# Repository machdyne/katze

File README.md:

# Katze Ethernet Pmod&trade; compatible module

Katze is a 10/100 Ethernet PHY PMOD designed to be compatible with LiteX.

This repo contains schematics, pinouts and usage examples.

Find more information on the [Katze product page](https://machdyne.com/product/katze-ethernet-pmod/).

## Usage

### Example Litex Platform Configuration

```
	("eth_clocks", 0,
		Subsignal("ref_clk", Pins("PMOD:7")),
		IOStandard("LVCMOS33")
	),
	("eth", 0,
		Subsignal("rx_data", Pins("PMOD:4 PMOD:5"), Misc("PULLMODE=UP")),
		Subsignal("tx_data", Pins("PMOD:0 PMOD:1")),
		Subsignal("tx_en", Pins("PMOD:2")),
		Subsignal("crs_dv", Pins("PMOD:3"), Misc("PULLMODE=UP")),
		Subsignal("rst_n", Pins("PMOD:6")),
		IOStandard("LVCMOS33")
	)
```

### Example LiteX Target Configuration

```
	from liteeth.phy.rmii import LiteEthPHYRMII
	self.submodules.ethphy = LiteEthPHYRMII(
		clock_pads = platform.request("eth_clocks"),
		pads = platform.request("eth"),
		with_hw_init_reset=True,
		refclk_cd=None)
	self.add_ethernet(phy=self.ethphy)
```

## Pinout

| Pin | Signal |
| --- | ------ |
| 1 | E\_TXD0 |
| 2 | E\_TXD1 |
| 3 | E\_TXEN |
| 4 | E\_CRS\_DV |
| 5 | GND |
| 6 | PWR3V3 |
| 7 | E\_RXD0 |
| 8 | E\_RXD1 |
| 9 | E\_RST\_N |
| 10 | CLK50 |
| 11 | GND |
| 12 | PWR3V3 |

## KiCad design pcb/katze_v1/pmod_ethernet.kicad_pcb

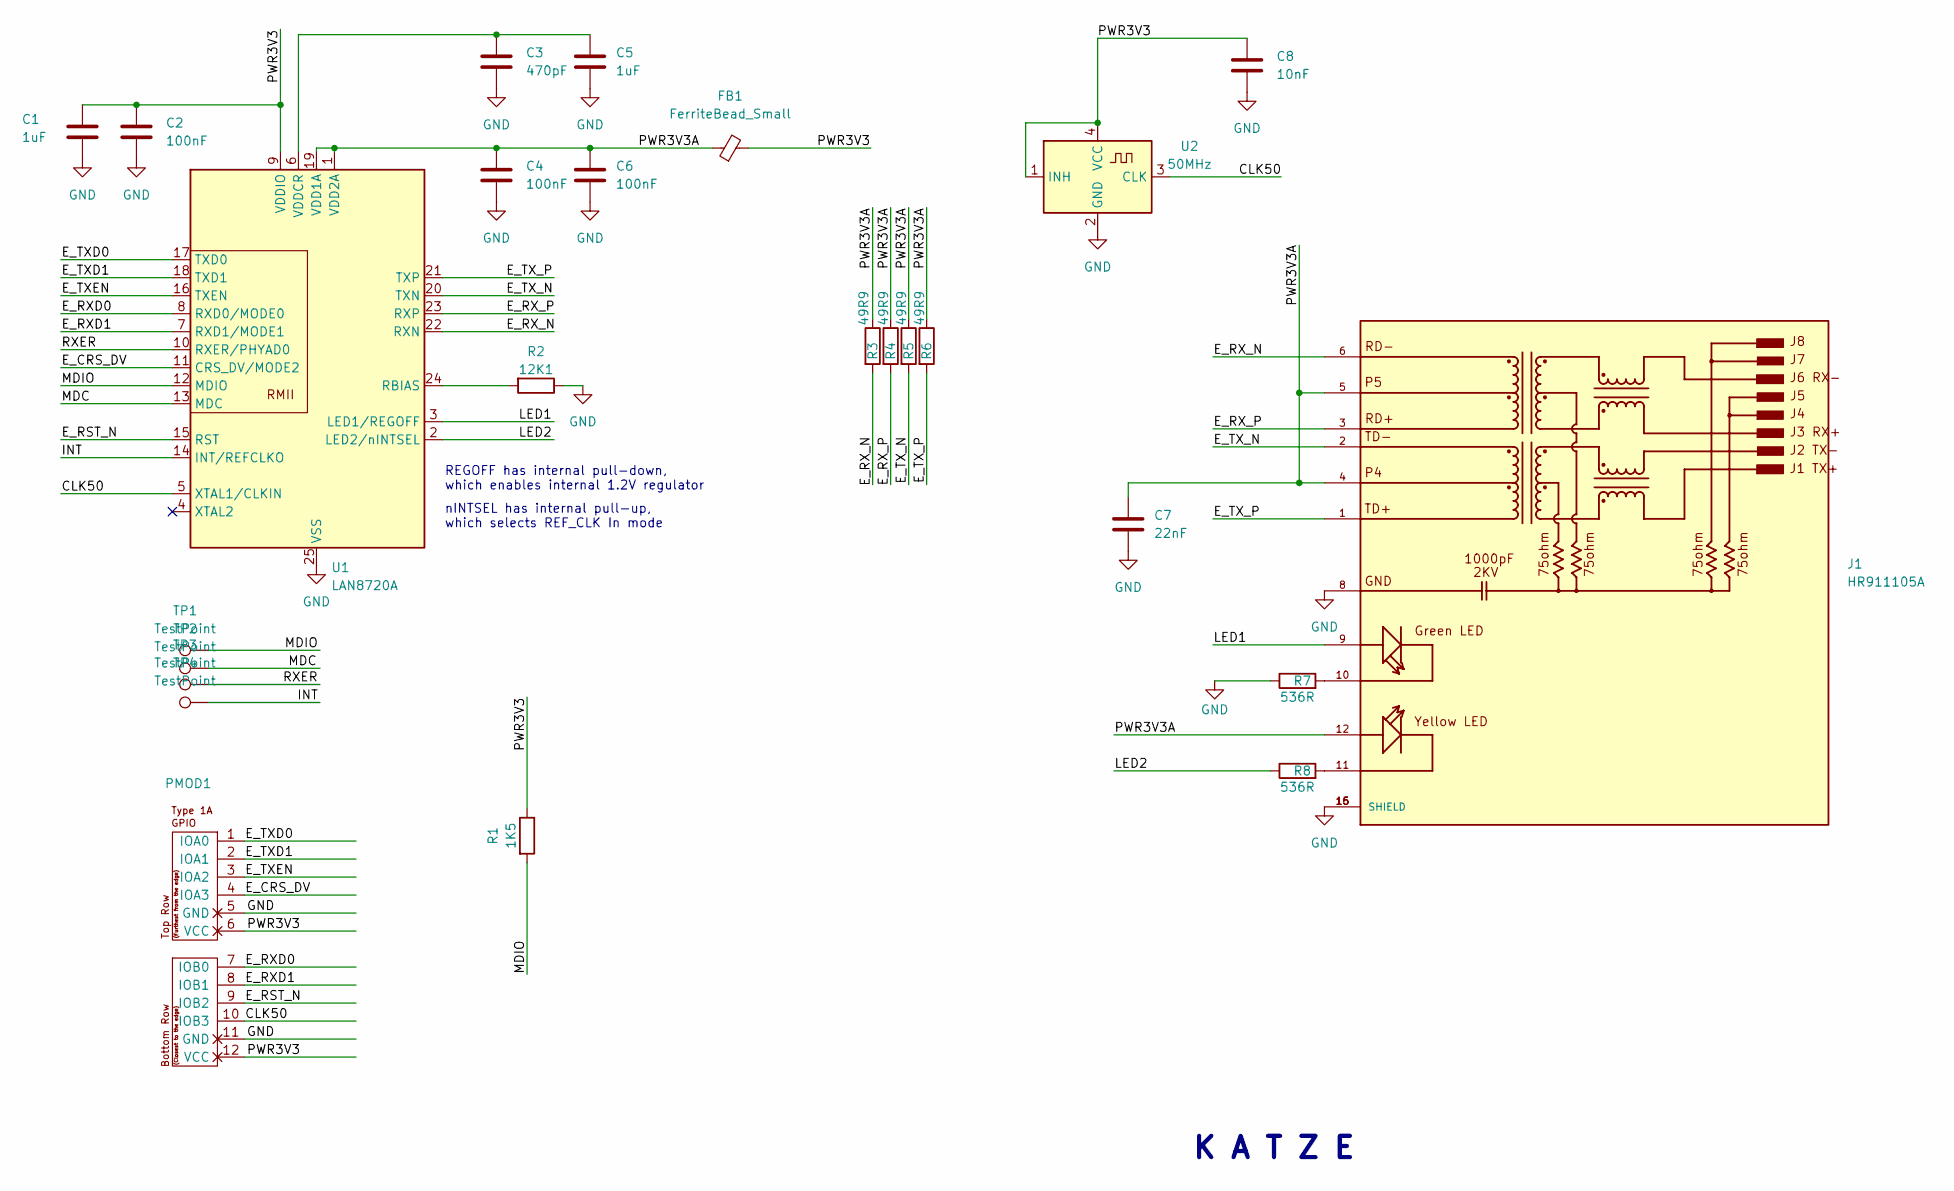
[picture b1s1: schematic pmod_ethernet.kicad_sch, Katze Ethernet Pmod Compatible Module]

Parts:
C1, C5: 1uF; C_0402_1005Metric
C2, C4, C6: 100nF; C_0402_1005Metric
C3: 470pF; C_0603_1608Metric
C7: 22nF; C_0603_1608Metric
C8: 10nF; R_0402_1005Metric
FB1: FerriteBead_Small; R_0402_1005Metric
J1: HR911105A; HANRUN_HR911105A; PARTREV A
PMOD1: PMOD-Device-x2-Type-1A-GPIO; pmod_pin_array_6x2
R1: 1K5; R_0402_1005Metric
R2: 12K1; R_0603_1608Metric
R3, R4, R5, R6: 49R9; R_0603_1608Metric
R7, R8: 536R; R_0402_1005Metric
TP1, TP2, TP3, TP4: TestPoint; TestPoint_Pad_1.0x1.0mm
U1: LAN8720A; QFN-24-1EP_4x4mm_P0.5mm_EP2.6x2.6mm
U2: 50MHz; Oscillator_SMD_Kyocera_KC2520Z-4Pin_2.5x2.0mm

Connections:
/CLK50: PMOD1.10 (IOB3), U1.5 (XTAL1/CLKIN), U2.3 (CLK)
/E_CRS_DV: PMOD1.4 (IOA3), U1.11 (CRS_DV/MODE2)
/E_RST_N: PMOD1.9 (IOB2), U1.15 (RST)
/E_RXD0: PMOD1.7 (IOB0), U1.8 (RXD0/MODE0)
/E_RXD1: PMOD1.8 (IOB1), U1.7 (RXD1/MODE1)
/E_RX_N: J1.6, R3.2, U1.22 (RXN)
/E_RX_P: J1.3, R4.2, U1.23 (RXP)
/E_TXD0: PMOD1.1 (IOA0), U1.17 (TXD0)
/E_TXD1: PMOD1.2 (IOA1), U1.18 (TXD1)
/E_TXEN: PMOD1.3 (IOA2), U1.16 (TXEN)
/E_TX_N: J1.2, R5.2, U1.20 (TXN)
/E_TX_P: J1.1, R6.2, U1.21 (TXP)
/INT: TP4.1, U1.14 (INT/REFCLKO)
/LED1: J1.9, U1.3 (LED1/REGOFF)
/LED2: R8.1, U1.2 (LED2/nINTSEL)
/MDC: TP2.1, U1.13 (MDC)
/MDIO: R1.2, TP1.1, U1.12 (MDIO)
/PWR3V3: C1.1, C2.1, C8.1, FB1.2, PMOD1.6 (VCC), PMOD1.12 (VCC), R1.1, U1.9 (VDDIO), U2.1 (INH), U2.4 (VCC)
/PWR3V3A: C4.1, C6.1, C7.1, FB1.1, J1.4, J1.5, J1.12, R3.1, R4.1, R5.1, R6.1, U1.1 (VDD2A), U1.19 (VDD1A)
/RXER: TP3.1, U1.10 (RXER/PHYAD0)
GND: C1.2, C2.2, C3.2, C4.2, C5.2, C6.2, C7.2, C8.2, J1.8, J1.15 (SHIELD), J1.16 (SHIELD), PMOD1.5 (GND), PMOD1.11 (GND), R2.1, R7.1, U1.25 (VSS), U2.2 (GND)
unnamed: C3.1, C5.1, U1.6 (VDDCR)
unnamed: J1.10, R7.2
unnamed: J1.11, R8.2
unnamed: R2.2, U1.24 (RBIAS)

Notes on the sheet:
nINTSEL has internal pull-up, which selects REF_CLK In mode
REGOFF has internal pull-down, which enables internal 1.2V regulator
K A T Z E

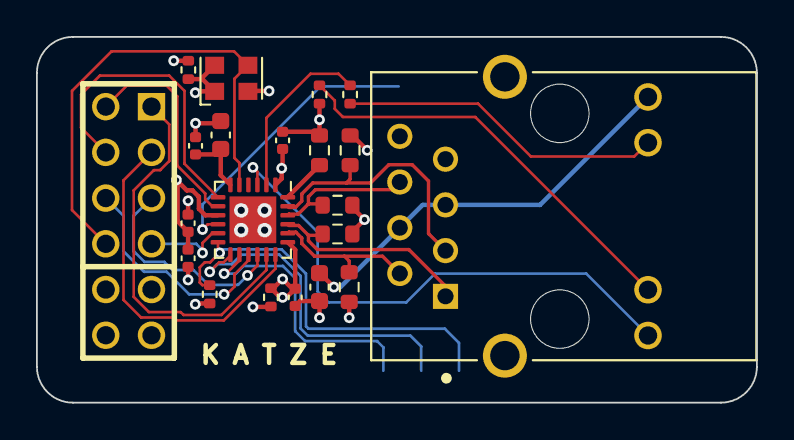
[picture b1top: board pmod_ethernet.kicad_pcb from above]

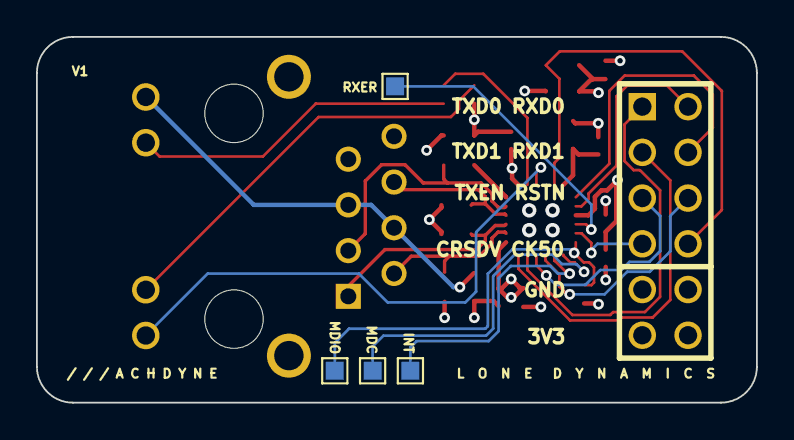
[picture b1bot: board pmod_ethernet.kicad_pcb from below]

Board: 4 copper layers, 40.0 x 20.3 mm, 25 parts (4 on the bottom side), 25 nets.

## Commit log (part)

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2023-01-03 add image
2023-02-01 update schematics

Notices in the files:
pcb/katze_v1/pmod_ethernet.kicad_sch:
Copyright © 2022 Lone Dynamics Corporation
